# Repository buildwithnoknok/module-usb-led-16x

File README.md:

# noknok LEDs 16x

A USB-controlled **round** ring of 16 RGBW LEDs for the noknok ecosystem. The Raspberry Pi
Pico drives it as a **USB host**; it can also be driven directly from a PC.

> **Sibling module:** the 8-LED RGB version lives in
> [`module-usb-led`](https://github.com/buildwithnoknok/module-usb-led). Both are being kept
> until the 16x boards arrive and the real optical difference (luminosity, colour, power
> draw) can be measured on the bench.

## Features
- **16× RGBW LEDs** (OPSCO `SKC6812RGBW-NW`, LCSC `C5348912`) — four channels per LED
  (R, G, B **and a dedicated white**), not three
- Round board, 96 components, double-sided assembly
- CH32V203G6U6 microcontroller, USB 1.1 (CDC) device
- USB-C power + data; Qwiic/Stemma-QT I2C pass-through
- **Unique per-unit USB serial** derived from the chip UID — so the Conductor can tell
  identical modules apart and map them to roles (the USB counterpart of the I2C UID)

## Status
- **Hardware: rev 2.0 — pilot boards received (Sep 2026).** Known issue: an audible "rustle"
  at high brightness from the 22 µF ceramic capacitors on `+5V` (C29/C36/C37) — fix proposed
  for rev 2.1 (see [`firmware/readme.md`](firmware/readme.md) → Power).
- **Firmware: v2.2.1 (own module type `0x06`) — bench-validated 2 Oct 2026:** all 16 LEDs × 4 channels, animations,
  LED-rail power switching, lossless USB receive, and a **power governor** (USB-C CC source
  limit, VBUS sag protection, **temperature protection** with the chip's calibrated sensor).
  `0x30 GET_STATUS` reports temperature/power for the app. Updates over USB (OTA).
- **Heat:** full power (1.8 W) in open air settles at ~57–58 °C chip temperature;
  measurements in [`docs/measurements/`](docs/measurements/). Thermal thresholds are
  provisional until measured inside the real housing.
- **Still to do:** Pico driver (`noknok_usb.py`) for 16 LEDs + white + `GET_STATUS`, and the
  read-only temperature field in the app (Sue); heat test in the real housing; animations aware
  of the 12 + 4 LED layout; port to the two-stage bootloader; rev 2.1 capacitor fix.

## How it's controlled

### From a Raspberry Pi Pico (USB host) — the noknok Conductor
The Pico hosts the module over PIO-USB (D+ → GP16, D− → GP17, behind a **powered** hub
such as the DataHub). The `NoknokLEDs` driver lives in
[`brain-Pico/software/noknok_usb.py`](https://github.com/buildwithnoknok/brain-Pico/tree/main/software)
and is discovered by the Conductor:

```python
from noknok import Conductor

c = Conductor()
c.enumerate_usb()          # brings up the USB host port, finds all LED modules
# (use c.enumerate_all() for a product that mixes I2C + USB modules)

# NOTE: the Pico driver still speaks the 8-LED RGB protocol - 16x/white support pending
leds = c.leds[0]                                  # or c.by_uid("<serial>"), or c.role["lamp"]
leds.set_all(255, 0, 0)                           # all red
leds.set_pixel(3, 0, 255, 0)                      # LED 3 green
leds.set_brightness(128)                          # global brightness
leds.set_led(0xFF, 0, 0, 255, brightness=200, duration_ms=1000)  # all blue 1 s, then off
leds.play_preset(leds.PRESET_RAINBOW, speed=40)  # non-blocking animation on the module
leds.play_preset(leds.PRESET_SUNDOWN, speed=30, r=0, g=0, b=255)  # 30 min fade to off, blue
leds.off()
```

Each module carries a unique serial, so multiple LED modules on one hub are addressed
individually. See **[Ecosystem → enumeration.md](https://github.com/buildwithnoknok/Ecosystem/blob/main/software/enumeration.md)**
(USB Module Discovery & Identity) and **[roles.md](https://github.com/buildwithnoknok/Ecosystem/blob/main/software/roles.md)**
(role assignment — this is an *output* module, assigned by cue-and-confirm).

### From a PC
PowerShell / Python helpers in [`tools/`](tools) (`noknok_leds.ps1`, `noknok_leds_pc.py`)
auto-detect the module and expose the same commands.

## Repository Structure
- `/hardware` — KiCad files, schematics, 3D models
- `/firmware` — source (`src/`), built binaries (`bin/`), and the firmware change record (`readme.md`)
- `/tools` — PC control scripts

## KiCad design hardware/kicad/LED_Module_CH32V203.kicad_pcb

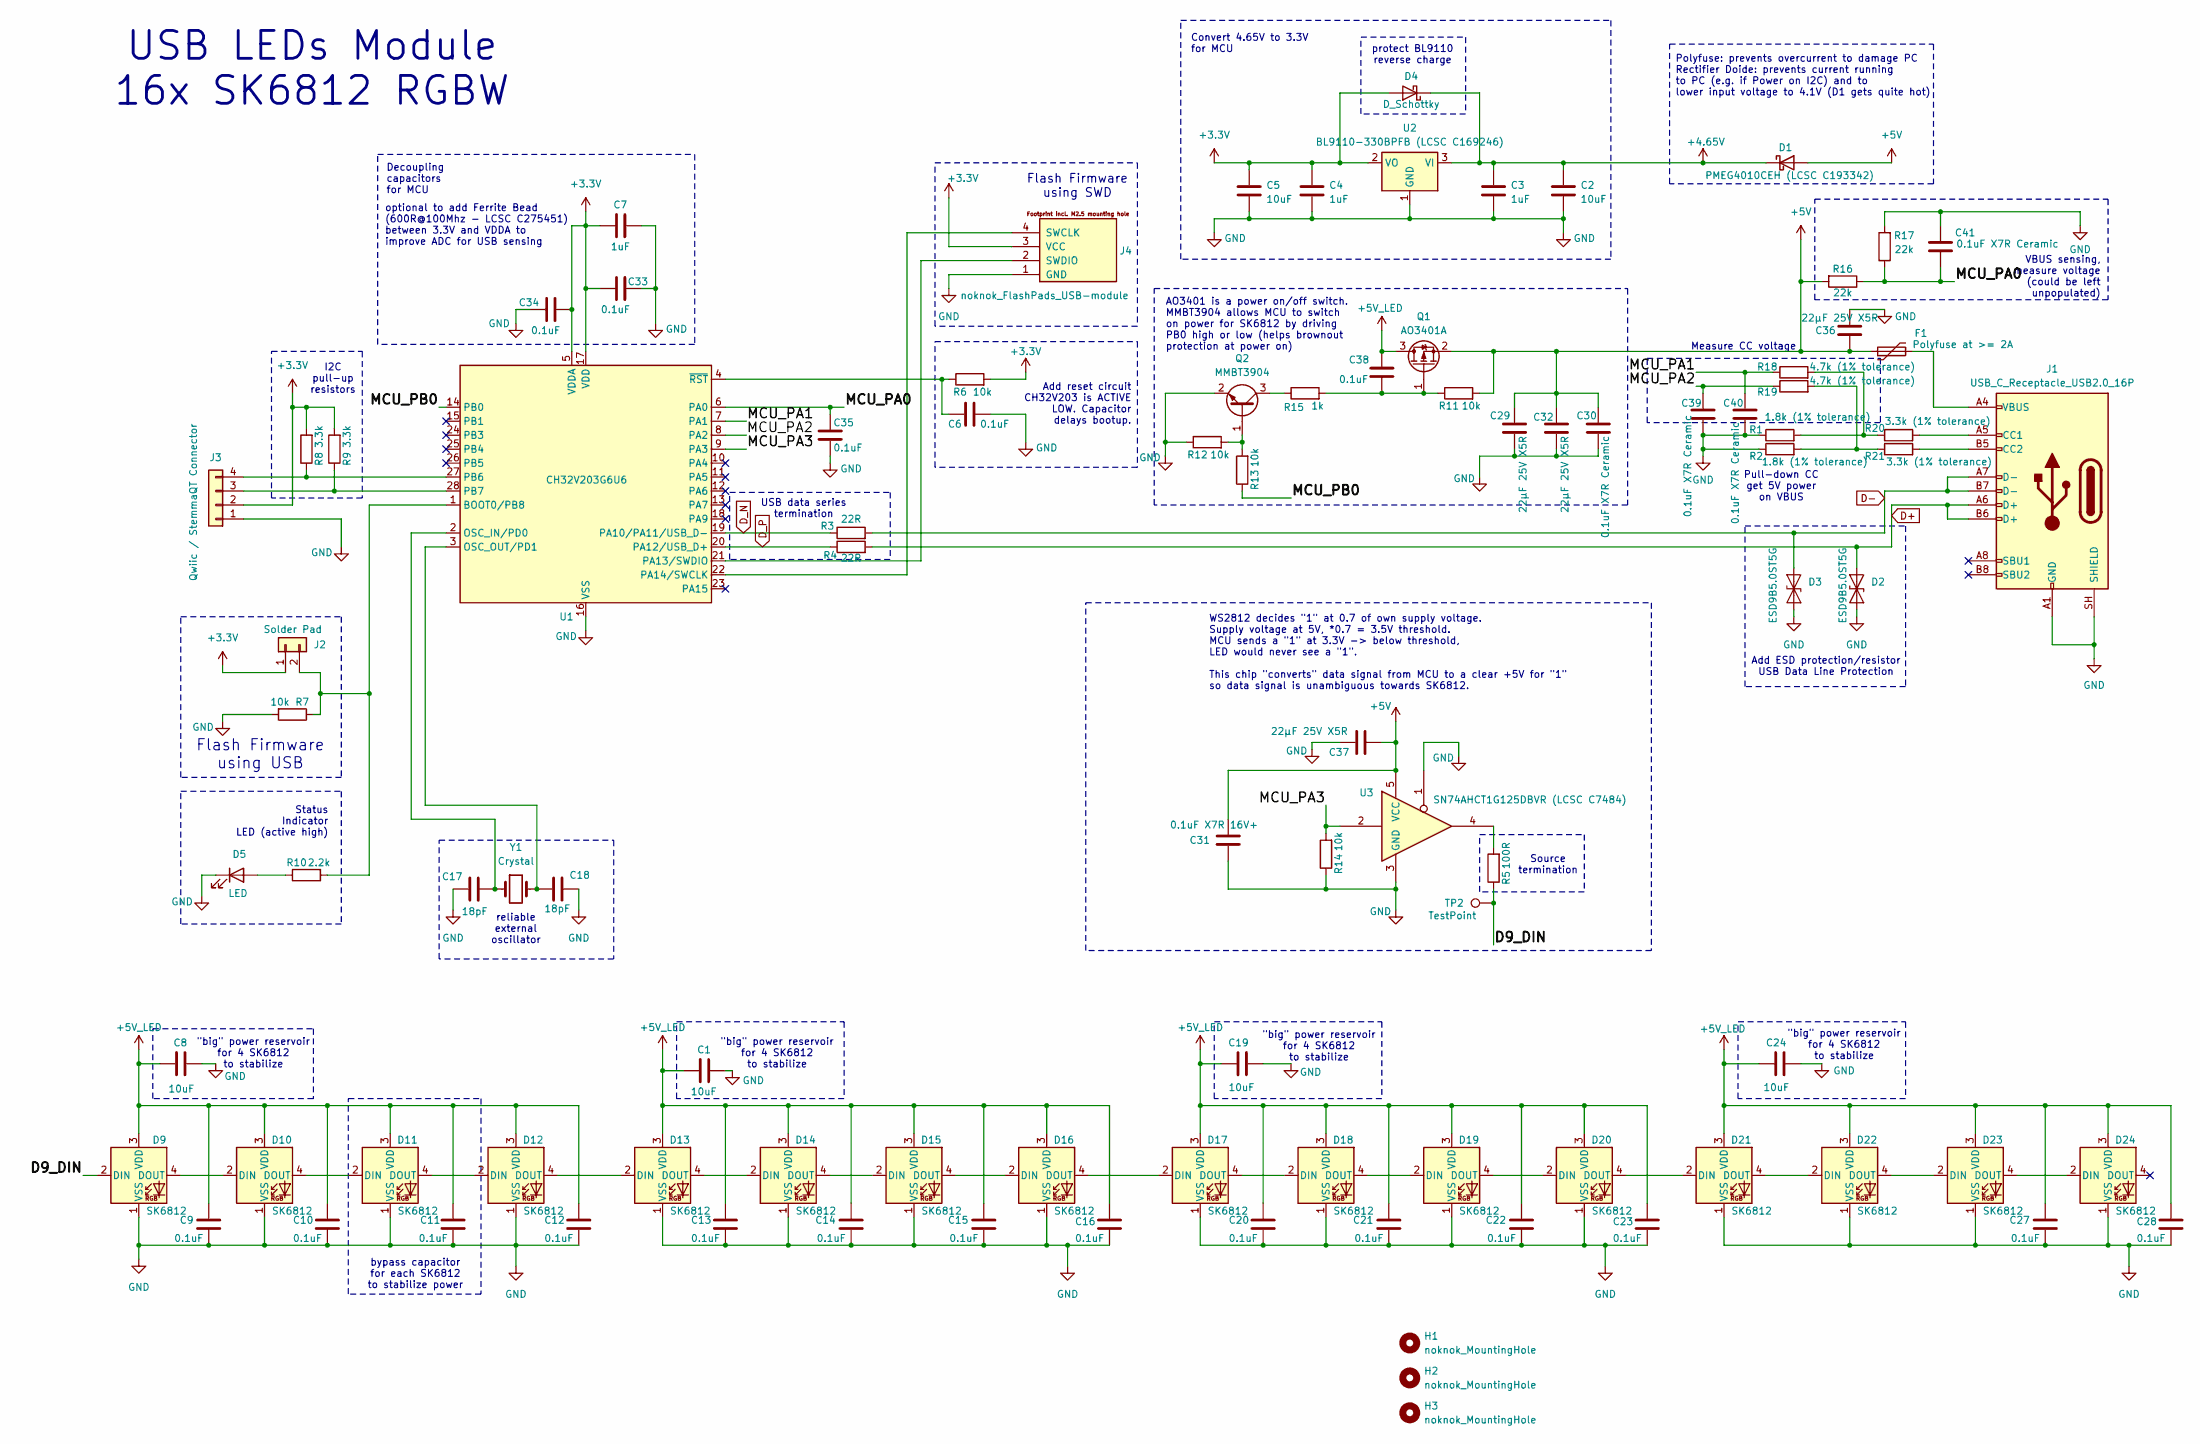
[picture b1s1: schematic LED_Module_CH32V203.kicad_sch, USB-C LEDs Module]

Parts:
C1, C2, C5, C8, C19, C24: 10uF; C_0603_1608Metric
C3, C4, C7: 1uF; C_0603_1608Metric
C6, C9, C10, C11, C12, C13, C14, C15, C16, C20, C21, C22, C23, C27, C28, C33, C34, C35, C38: 0.1uF; C_0603_1608Metric
C17, C18: 18pF; C_0603_1608Metric
C29, C32, C36, C37: 22µF 25V X5R; C_1206_3216Metric
C30, C39, C40, C41: 0.1uF X7R Ceramic; C_0603_1608Metric
C31: 0.1uF X7R 16V+; C_0603_1608Metric
D1: PMEG4010CEH (LCSC C193342); D_SOD-123
D2, D3: ESD9B5.0ST5G; D_SOD-923
D4: D_Schottky; D_SOD-323
D5: LED; LED_0603_1608Metric
D9, D10, D11, D12, D13, D14, D15, D16, D17, D18, D19, D20, D21, D22, D23, D24: SK6812; LED_SK6812_PLCC4_5.0x5.0mm_P3.2mm
F1: Polyfuse at >= 2A; Fuse_1206_3216Metric
H1, H2, H3: noknok_MountingHole; noknok_MountingHole_2.5mm_M2.5
J1: USB_C_Receptacle_USB2.0_16P
J2: Solder Pad; SolderJumper-2_P1.3mm_Open_TrianglePad1.0x1.5mm
J3: Qwiic / StemmaQT Connector; JST_SH_SM04B-SRSS-TB_1x04-1MP_P1.00mm_Horizontal_CHRIS
J4: noknok_FlashPads_USB-module; noknok_FlashPads_USB-module_1x4_M2.5
Q1: AO3401A; SOT-23
Q2: MMBT3904; SOT-23
R1, R2: 1.8k (1% tolerance); R_0603_1608Metric
R3, R4: 22R; R_0603_1608Metric
R5: 100R; R_0603_1608Metric
R6, R7, R11, R12, R13, R14: 10k; R_0603_1608Metric
R8, R9: 3.3k; R_0603_1608Metric
R10: 2.2k; R_0603_1608Metric
R15: 1k; R_0603_1608Metric
R16, R17: 22k; R_0603_1608Metric
R18, R19: 4.7k (1% tolerance); R_0603_1608Metric
R20, R21: 3.3k (1% tolerance); R_0603_1608Metric
TP2: TestPoint; TestPoint_THTPad_D1.0mm_Drill0.5mm
U1: CH32V203G6U6; WQFN-28-1EP_4x4mm_P0.4mm_EP2.7x2.7mm
U2: BL9110-330BPFB (LCSC C169246); SOT-223-3_TabPin2
U3: SN74AHCT1G125DBVR (LCSC C7484); SOT-23-5
Y1: Crystal; Crystal_SMD_3225-4Pin_3.2x2.5mm

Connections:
+3.3V: C4.1, C5.1, C7.1, C33.1, C34.2, D4.2 (A), J2.1, J3.2, J4.3 (VCC), R6.2, R8.2, R9.2, U1.5 (VDDA), U1.17 (VDD), U2.2 (VO)
+4.65V: C2.1, C3.1, D1.1 (K), D4.1 (K), U2.3 (VI)
+5V: C29.1, C30.1, C31.1, C32.1, C36.2, C37.2, D1.2 (A), F1.1, Q1.2 (S), R11.2, R16.2, U3.5 (VCC)
+5V_LED: C1.1, C8.1, C9.1, C10.1, C11.1, C12.1, C13.1, C14.1, C15.1, C16.1, C19.1, C20.1, C21.1, C22.1, C23.1, C24.1, C27.1, C28.1, C38.1, D9.3 (VDD), D10.3 (VDD), D11.3 (VDD), D12.3 (VDD), D13.3 (VDD), D14.3 (VDD), D15.3 (VDD), D16.3 (VDD), D17.3 (VDD), D18.3 (VDD), D19.3 (VDD), D20.3 (VDD), D21.3 (VDD), D22.3 (VDD), D23.3 (VDD), D24.3 (VDD), Q1.3 (D)
/D9_DIN: D9.2 (DIN), R5.1, TP2.1 (1_1)
/MCU_PA0: C35.1, C41.2, R16.1, R17.1, U1.6 (PA0)
/MCU_PA1: C40.1, R18.1, U1.7 (PA1)
/MCU_PA2: C39.1, R19.1, U1.8 (PA2)
/MCU_PA3: R14.2, U1.9 (PA3), U3.2
/MCU_PB0: R13.1, U1.14 (PB0)
D+: D2.1 (A1), J1.A6 (D+), J1.B6 (D+), R4.2
D-: D3.1 (A1), J1.A7 (D-), J1.B7 (D-), R3.2
D_N: R3.1, U1.19 (PA10/PA11/USB_D-)
D_P: R4.1, U1.20 (PA12/USB_D+)
GND: C1.2, C2.2, C3.2, C4.2, C5.2, C6.1, C7.2, C8.2, C9.2, C10.2, C11.2, C12.2, C13.2, C14.2, C15.2, C16.2, C17.1, C18.1, C19.2, C20.2, C21.2, C22.2, C23.2, C24.2, C27.2, C28.2, C29.2, C30.2, C31.2, C32.2, C33.2, C34.1, C35.2, C36.1, C37.1, C39.2, C40.2, C41.1, D2.2 (A2), D3.2 (A2), D5.1 (K), D9.1 (VSS), D10.1 (VSS), D11.1 (VSS), D12.1 (VSS), D13.1 (VSS), D14.1 (VSS), D15.1 (VSS), D16.1 (VSS), D17.1 (VSS), D18.1 (VSS), D19.1 (VSS), D20.1 (VSS), D21.1 (VSS), D22.1 (VSS), D23.1 (VSS), D24.1 (VSS), J1.A1 (GND), J1.A12 (GND), J1.B1 (GND), J1.B12 (GND), J1.SH (SHIELD), J3.1, J4.1 (GND), Q2.2 (E), R1.1, R2.1, R7.2, R12.1, R14.1, R17.2, U1.16 (VSS), U1.29 (VSS), U2.1 (GND), U3.1, U3.3 (GND)
unnamed: D5.2 (A), R10.1
unnamed: D9.4 (DOUT), D10.2 (DIN)
unnamed: D10.4 (DOUT), D11.2 (DIN)
unnamed: D11.4 (DOUT), D12.2 (DIN)
unnamed: D12.4 (DOUT), D13.2 (DIN)
unnamed: D13.4 (DOUT), D14.2 (DIN)
unnamed: D14.4 (DOUT), D15.2 (DIN)
unnamed: D15.4 (DOUT), D16.2 (DIN)
unnamed: D16.4 (DOUT), D17.2 (DIN)
unnamed: D17.4 (DOUT), D18.2 (DIN)
unnamed: D18.4 (DOUT), D19.2 (DIN)
unnamed: D19.4 (DOUT), D20.2 (DIN)
unnamed: D20.4 (DOUT), D21.2 (DIN)
unnamed: D21.4 (DOUT), D22.2 (DIN)
unnamed: D22.4 (DOUT), D23.2 (DIN)
unnamed: D23.4 (DOUT), D24.2 (DIN)
unnamed: F1.2, J1.A4 (VBUS), J1.A9 (VBUS), J1.B4 (VBUS), J1.B9 (VBUS)
unnamed: J1.A5 (CC1), R20.2
unnamed: J1.B5 (CC2), R21.2
unnamed: J2.2, R7.1, R10.2, U1.1 (BOOT0/PB8)
unnamed: J3.3, R9.1, U1.28 (PB7)
unnamed: J3.4, R8.1, U1.27 (PB6)
unnamed: J4.4 (SWCLK), U1.22 (PA14/SWCLK)
unnamed: J4.2 (SWDIO), U1.21 (PA13/SWDIO)
unnamed: C38.2, Q1.1 (G), R11.1, R15.2
unnamed: Q2.1 (B), R12.2, R13.2
unnamed: Q2.3 (C), R15.1
unnamed: R1.2, R18.2, R20.1
unnamed: R5.2, U3.4
unnamed: R2.2, R19.2, R21.1
unnamed: C17.2, U1.2 (OSC_IN/PD0), Y1.1
unnamed: C18.2, U1.3 (OSC_OUT/PD1), Y1.2
unnamed: C6.2, R6.1, U1.4 (~RST)

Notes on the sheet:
Polyfuse: prevents overcurrent to damage PC Rectifier Doide: prevents current running to PC (e.g. if Power on I2C) and to lower input voltage to 4.1V (D1 gets quite hot)
Pull-down CC get 5V power on VBUS
"big" power reservoir for 4 SK6812 to stabilize
Source termination
Add reset circuit CH32V203 is ACTIVE LOW. Capacitor delays bootup.
USB data series termination
Measure CC voltage
optional to add Ferrite Bead (600R@100Mhz - LCSC C275451) between 3.3V and VDDA to improve ADC for USB sensing
Decoupling capacitors for MCU
VBUS sensing, measure voltage (could be left unpopulated)
reliable external oscillator
Status Indicator LED (active high)
WS2812 decides "1" at 0.7 of own supply voltage. Supply voltage at 5V, *0.7 = 3.5V threshold. MCU sends a "1" at 3.3V -> below threshold, LED would never see a "1". This chip "converts" data signal from MCU to a clear +5V for "1" so data signal is unambiguous towards SK6812.
Flash Firmware using USB
USB LEDs Module 16x SK6812 RGBW
Flash Firmware using SWD
Add ESD protection/resistor USB Data Line Protection
AO3401 is a power on/off switch. MMBT3904 allows MCU to switch on power for SK6812 by driving PB0 high or low (helps brownout protection at power on)
Convert 4.65V to 3.3V for MCU
protect BL9110 reverse charge
bypass capacitor for each SK6812 to stabilize power
I2C pull-up resistors

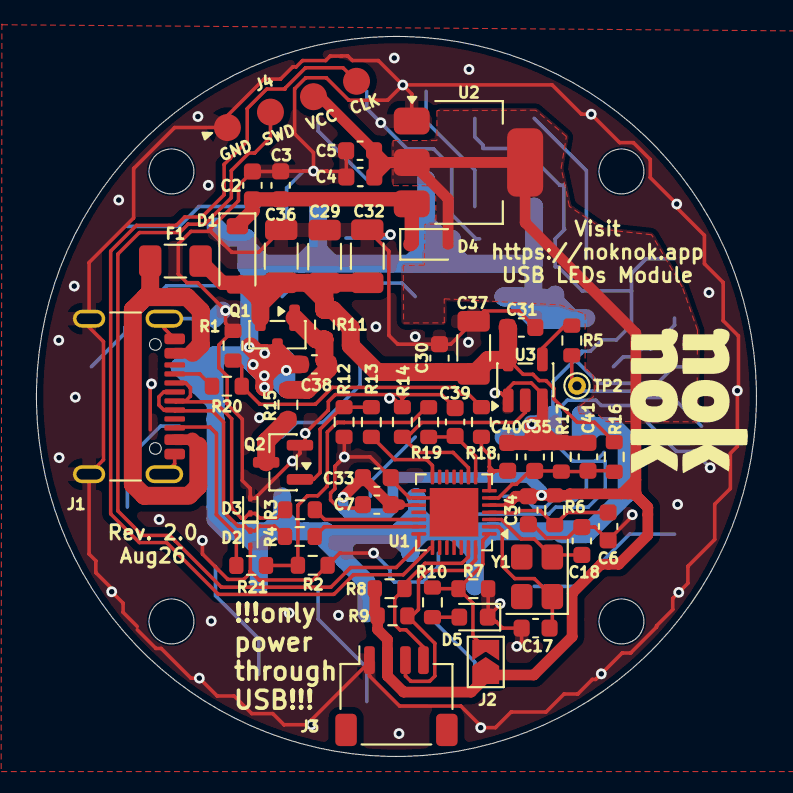
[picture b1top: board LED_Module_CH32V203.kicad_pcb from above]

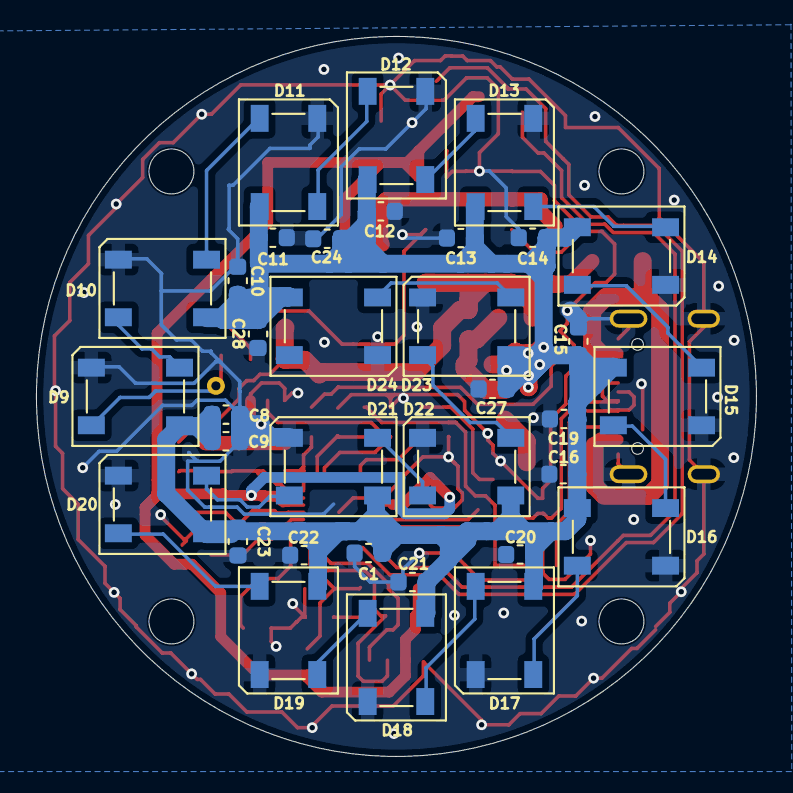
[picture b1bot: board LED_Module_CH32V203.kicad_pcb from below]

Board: 2 copper layers, 40.0 x 40.0 mm, 96 parts (34 on the bottom side), 48 nets.

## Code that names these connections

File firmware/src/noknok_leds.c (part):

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 * USB:   USBD (FSDEV) controller via extralibs/usbd.c - the SAME controller the
 *        WCH bootloader uses (D+ pull-up via EXTEN_USBD_PU_EN).
 *        48 MHz core -> USBPRE=DIV1 -> 48 MHz USB clock.
 * LEDs:  16x SK6812 RGBW (GRBW, 32 bit/LED) on PA3 via TIM2_CH4 PWM + DMA1_Channel2.
 *        Hardware timer generates every bit - NO bit-banging, CPU not involved.
 * POWER: PB0 = LED-rail load switch (HIGH = on). PA3 must NEVER be high while the
 *        rail is off (level shifter U3 is always enabled -> would back-feed the
 *        dead rail through the LED DIN clamp). See led_rail_*() below.
 * STATUS: PB8 = status LED (active-high, also BOOT0) - held low by the app.
 * TIME:  TIM3 free-running 1 kHz (1 ms/tick) timebase for durations + animations.
 *
 * v2.0.0 changes (first firmware for the 16x RGBW board - NOT for the 8x board):
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 *     effect at the next bit boundary, so no pulse is ever clipped/stretched mid-bit
 *     (the 8x driver wrote the live register - a marginal-waveform risk, cf. LED Button).
 *   - DMA priority VERY HIGH.
 *   - LED rail sequencing on PB0: rail off at boot, switched on (then 1 ms settle)
 *     before the first non-black frame, switched off again when the frame is all black.
 *   - Current cap: total LED current is estimated per frame and everything is scaled
 *     down if it would exceed LED_BUDGET_MA (450 mA = safe on a USB-2.0 port).
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 *     now runs uncapped; only near-full all-channel frames are limited.
 *
 * v2.1.0 changes (29 Sep 2026) - power governor, first half of 'step 3':
 *   - ADC1 reads VBUS (PA0), CC1/CC2 (PA1/PA2), die temperature (ch16) and VREFINT
 *     (ch17, for true mV) 10x per second.
 *   - LED budget = source limit from the CC pins (default 450 / 1.5 A + 3 A: 1000 mA)
 *     x VBUS factor (dims while VBUS sags, cuts the LED rail below VBUS_CUT_MV)
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 * v2.2.0 (29 Sep 2026): OWN MODULE TYPE 0x06. 0xF0 now answers 4E 4E 06 (was 04,
 *   shared with the 8x board). Hosts that only know 0x04 no longer mistake it for an 8x.
 *
 * v2.2.1 (2 Oct 2026, DEV-28): ws_show() refuses to send LED data unless PB0's output
 *   register says the LED rail is on - the PA3/PB0 rule is now a hard check in the
 *   driver, not only a property of how show() is written.
 *   FIX: CC1/CC2 are read through the board's 3.3k/1.8k Rd divider (PA1/PA2 see
 *   CC x 1.8/5.1); now scaled back to the real CC voltage. Before, a 3 A USB-C source
 *   (CC 1.63 V) read 0.57 V and was treated as default USB (budget stuck at 450 mA).
 *   GET_STATUS CC1/CC2 now report the real line voltage.
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
/* ============================================================
 * Pins that must be safe from the very first instruction
 *   PA3 = LED data (TIM2_CH4) - driven LOW as plain GPIO until the timer owns it
 *   PB0 = LED-rail enable     - LOW = rail off
 *   PB8 = status LED          - LOW = off
 * ============================================================ */
static void pins_safe_init(void) {
    RCC->APB2PCENR |= RCC_APB2Periph_AFIO | RCC_APB2Periph_GPIOA | RCC_APB2Periph_GPIOB;
    GPIOA->BCR = (1u << 3);                                             /* PA3 low  */
    GPIOA->CFGLR = (GPIOA->CFGLR & ~(0xFUL << 12)) | (0x3UL << 12);     /* PA3 out PP 50MHz */
    GPIOB->BCR = (1u << 0) | (1u << 8);                                 /* PB0, PB8 low */
    GPIOB->CFGLR = (GPIOB->CFGLR & ~(0xFUL << 0)) | (0x3UL << 0);       /* PB0 out PP */
    GPIOB->CFGHR = (GPIOB->CFGHR & ~(0xFUL << 0)) | (0x3UL << 0);       /* PB8 out PP */
}

/* ============================================================
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
    TIM2->CTLR1 |= TIM_CEN;                   /* free-running; output low while CCR=0 */

    /* Hand PA3 to the timer only now - the timer output is already low (CCR=0),
     * so the pin never glitches high. AF push-pull 50 MHz. */
    GPIOA->CFGLR = (GPIOA->CFGLR & ~(0xFUL << 12)) | (0xBUL << 12);
}

static void ws_show(const uint8_t *grbw) {
    /* HARD INVARIANT (rev 2.0 board, DEV-28): never clock data out on PA3 while the
     * LED rail is off. U3 (level shifter) is always enabled, so a high on PA3 would
     * push ~4.9 V into the DIN of unpowered LEDs and back-feed the dead rail. Checked
     * against the PB0 OUTPUT REGISTER itself, not a software flag, so no caller or
     * future code path can get around it. */
    if (!(GPIOB->OUTDR & (1u << 0))) return;
    ws_build_buf(grbw);
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}

/* ============================================================
 * LED rail (PB0) - never drive data into an unpowered LED
 * ============================================================ */
static uint8_t rail_on = 0;

static void led_rail_on(void) {
    if (rail_on) return;
    GPIOB->BSHR = (1u << 0);                  /* PB0 high -> Q2/Q1 switch the rail on */
    Delay_Ms(1);                              /* soft start ~160 us + LED power-on reset */
    rail_on = 1;
}
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 * Sensors (ADC1) + power governor (v2.1.0)
 *
 * Inputs, read 10x per second:
 *   PA0  = VBUS via 22k/22k divider (x2)
 *   PA1  = CC1, PA2 = CC2 - ANALOG IN, NO pull-up/down (a pull would sit in
 *          parallel with the 5.1k Rd and break USB-C source detection)
 *   ch16 = internal temperature sensor, ch17 = VREFINT (1.20 V). VREFINT gives
 *          the real VDDA, so every reading is in true mV, not "fraction of 3.3 V".
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#define T_CUT_DC            750           /* LED power OFF at 75.0 C ... */
#define T_RESUME_DC         650           /* ... back on below 65.0 C */

/* VBUS (mV) - where PA0 sits relative to the input diode is not yet verified */
#define VBUS_DERATE_MV      4400          /* below: step brightness down */
#define VBUS_RECOVER_MV     4550          /* above: step back up */
#define VBUS_CUT_MV         4100          /* below: LED power OFF (keep MCU + USB alive) */
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static void adc_init(void) {
    RCC->APB2PCENR |= RCC_APB2Periph_ADC1 | RCC_APB2Periph_GPIOA;
    RCC->CFGR0 = (RCC->CFGR0 & ~RCC_ADCPRE) | RCC_ADCPRE_DIV4;       /* 48 / 4 = 12 MHz */
    GPIOA->CFGLR &= ~(0xFFFUL << 0);                                  /* PA0..PA2 analog, no pulls */
    ADC1->SAMPTR2 = 0x3FFFFFFF;           /* ch0-9   : 239.5 cycles (~20 us) */
    ADC1->SAMPTR1 = 0x00FFFFFF;           /* ch10-17 : 239.5 cycles (temp sensor needs >= 17 us) */
    ADC1->RSQR1   = 0;                    /* one conversion per start */
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static inline uint16_t raw_to_mv(uint16_t raw) { return (uint16_t)((uint32_t)raw * s_vdda_mv / 4095u); }

/* CC sense on the rev 2.0 board is NOT the CC pin itself: the 5.1k Rd is split into
 * 3.3k (R20/R21, connector side) + 1.8k (R1/R2, to GND) and PA1/PA2 tap the middle
 * through 4.7k (R18/R19, no current flows -> no error). So the ADC sees CC x 1.8/5.1.
 * Scale back to the real CC line voltage so the USB-C spec thresholds apply.
 * (Found 2 Oct 2026: a 3 A USB-C charger, CC1 = 1.63 V on the KWS-X1, read as
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static uint16_t gov_last;

int main(void) {
    pins_safe_init();         /* PA3 data low, LED rail off, status LED off - FIRST */
    clock_to_hse_48();        /* crystal-accurate 48 MHz first */
    build_serial();           /* fill iSerialNumber from chip UID before enumeration */
    USBDSetup();              /* FSDEV USB device (asserts EXTEN_USBD_PU_EN) */
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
